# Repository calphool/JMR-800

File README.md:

# JMR-800

**JMR-800** is a modern, open-source clone of the Roland PG-800 hardware programmer, built around the Teensy 4.1 microcontroller. It provides real-time 
parameter control for vintage Roland synthesizers such as the JX-8P, MKS-70, and JX-10 using the original PG-800 communication protocol.

The JMR-800 replicates the original PG-800's functionality and physical interface, enabling direct, tactile editing of synthesizer parameters through a 
hands-on control surface.

## Features

- Compatible with Roland synths that support the PG-800 interface
- Built on Teensy 4.1 with fast, low-latency signal handling
- Accurate emulation of the PG-800 protocol (Clock, Ready, and Data lines)
- Designed for easy assembly and expansion
- Open hardware and firmware

## Status

This project is currently in active development. Basic communication and parameter changes are being validated. Contributions, forks, and collaboration are 
welcome.

April 10, 2025

- Redesigned PCB to get rid of the 74HC165 input bit shifter and replaced it with another analog mux/demux.  The total number of parameters that can be 
tweaked with the JX8P with the Vecoven PWM enhancement is 52.  So, I need to support at least 52 pots, and I can only support 48 with three muxes.  I mean
there are enough ADCs on the Teensy 4.1, that I probably could hack it and get those last 4 with separate ADC pins on the Teensy, but that's a pretty 
ineligant design, so I'll just add another mux/demux, get rid of the bit shifter, and limit my use of push buttons to just a few.  I technically only 
need one or two (the PG-800 only has 2), but I'll probably come up with a few odds and ends to implement (like maybe a way to load a whole sound from 
the JMR-800 by tweaking all of the parameters based on loading something from an SD card or something), so having a few more won't hurt.

- Decided to lay out the whole interface with my 3D printer as a template first.  This will allow me to cut cleaner holes into the aluminum case I think.
I'm using an aluminum case from Jameco that looks pretty retro / period correct.

April 14, 2025

Worked on the aluminum case a bit today.  Ran out of potentiometers, so ordered some more.

April 17, 2025

Worked on the case some more.  Completed the potentiometer installation, got some knobs and installed them, though I don't like the fact that I didn't get 
an even number of red and blue, so I need to get another kit of them.  I also don't like the white ones, I think I'll remove those and replace with black.  
Finally, I couldn't find black 3mm screws, so I had to use stainless steel.  I'm going to change that, it ruins the asthetic.

Once I get all that settled, it's back to the software and firmware.  I redesigned the PCB about a week ago, but I think I'm going to need to do a slight 
additional redesign.  The four push buttons have two LEDs on them, a red one and a green one.  I really don't know exactly what I'm going to use them 
for yet, but I'm going to need an output shift register to manage all 8 of them (as well as current limiting resistors for each one, which would probably 
be best on the board rather than dangling and inline with the wires.

The software already works in a prototype way (two potentiometers that I tested with), so hopefully there won't be any surprises when I get all of them 
running.  I also added an additional 3.3V regulator that's optional on the new design, since I'm not altogether sure that the tiny little regulator on the 
Teensy can handle all the load I'm throwing at it.

April 29, 2025

Got the new PCB and the rest of the hardware put together.  I wrote some temporary code that implements a "TEST MODE" that shows the condition of all 
the knobs.

May 3, 2025

I've updated the code quite a bit.  It now has 3 modes.  Run mode, Test mode, and Config mode.  I've been working on the Config mode.  You can change 
into these different modes by pressing Button 1 and Button 2 simultaneously.  When you configure a knob, you can change its name, its command byte, 
and select which type of knob it is.  I've got the command byte selection finished, and I'm working on the name update code now.  Once I get all the 
config stuff finished (perhaps this evening), I'll begin working on the Run mode.  This stuff was prototyped already with the earlier version of the 
board, so I'm pretty sure the code for interacting with the synth will work.

I may eventually implement some kind of "preset mode" that allows you to scroll through a given configuration of knobs, select it, and it would play 
all 56 knobs into the synthesizer.  This may be a submenu of the Run mode.  One step at a time of course...

May 5, 2025

***It's alive***!  I got the first fully functional code put together and just did about 15 minutes of testing.  It definitely works.  Though there's 
plenty to tweak.  Right now it's ignoring the parameter type and just sending values from 0 - 127, which does work, but it causes the screen to flicker 
on the synth for the parameters that only have a few set values.  I'm also wondering about how to manage noise from the potentiometers.  Although I 
used a smoothing algorithm, which does make them a lot less noisy, you still get odd little blips from time to time, and since they take whatever 
value the knob is at at the time, if you've just changed patches it can make a dramatic change to the sound.  I wonder if I should implement a 
kind of "lock / unlock" with one of the switches.  I could use green for "I'm unlocked and sending data to the synth" vs red for "I'm currently 
locked and not sending anything to the synth."

Lots and lots of small tweaks to work on now, but at least it's working.  The PWM mod that I installed from https://www.vecoven.com/superjx/styled/pwm.html
is pretty cool, especially with knobs that tweak its behavior in real time.

The other tweaks that the vecoven upgrade made to my firmware on my synth still takes some getting used to.  I'm going to have to read through the 
manuals for the vecoven upgrade really carefully, because it's pretty easy to get lost in the menus.  Maybe I could implement a "notepad" in the 
OLED screen of the JMR800 so it can remind me of stuff for the Vecoven upgrade.

One thing that I noticed that I'm going to have to deal with is the fact that not all the pots return the full range from 0 - 127 when sent through the 
ADC.  They came in a big bag from Aliexpress, so they're probably pretty low quality.  I'm going to need to implement some way to measure their min and 
max values, probably in the config mode, and then scale the pot value for each pot in software.

May 11, 2025

Finished all the screen stuff for Run mode, which is a pretty big milestone.  Also added an SVG file that represents the console layout. Working on an 
overlay using a Glowforge and acrylic.

May 14, 2025

May 22, 2025

I'm beginning to consider a major refactor of the software.  It all works pretty well, but there are some things I'd like to do that require a cleaner code 
base.  Basically I cobbled together the different system modes using a sloppy FSM rather than doing proper object oriented development whereby I set up 
modes as objects, and modes have screens, and screens have widgets, and widgets interact with controls, and so on.  By doing this, I'd have an infinitely 
more expandable user interface, and I really would like to implement a few interesting ideas.

First, I'd like to make it so that there are a collection of pre-sets that can be played into the JX8P on demand (like button 2 does right now with the 
default sound load, but with many many different presets).  The other thing I'd really like to do is implement something analogous to an arpeggiator, but 
rather than changing notes, it would change settings on a parameter.  For example, let's say you want to vary any arbitrary parameter (say something weird 
like chorus) with something like an LFO.  Let us further consider that you don't want to use one of the three or four LFO options available in the synth 
hardware itself, bur instead you want to be able to apply any arbitrary waveform to that chorus.  Although the "waveform" will be small (only 32 steps), it 
can take any form, and you simply draw the waveform in.  Then, when you go to a parameter for a given control, you depress the encoder button, and it pops 
up with a menu that lets you choose which stepper-LFO you want to use for this parameter.

All of this will require some significant refactoring.  I also want to introduce a microSD to the Teensy so that all this stuff can be stored and retrieved.  
Keep an eye out for a major update to the code base soon.

## License

This project is released under the MIT License.

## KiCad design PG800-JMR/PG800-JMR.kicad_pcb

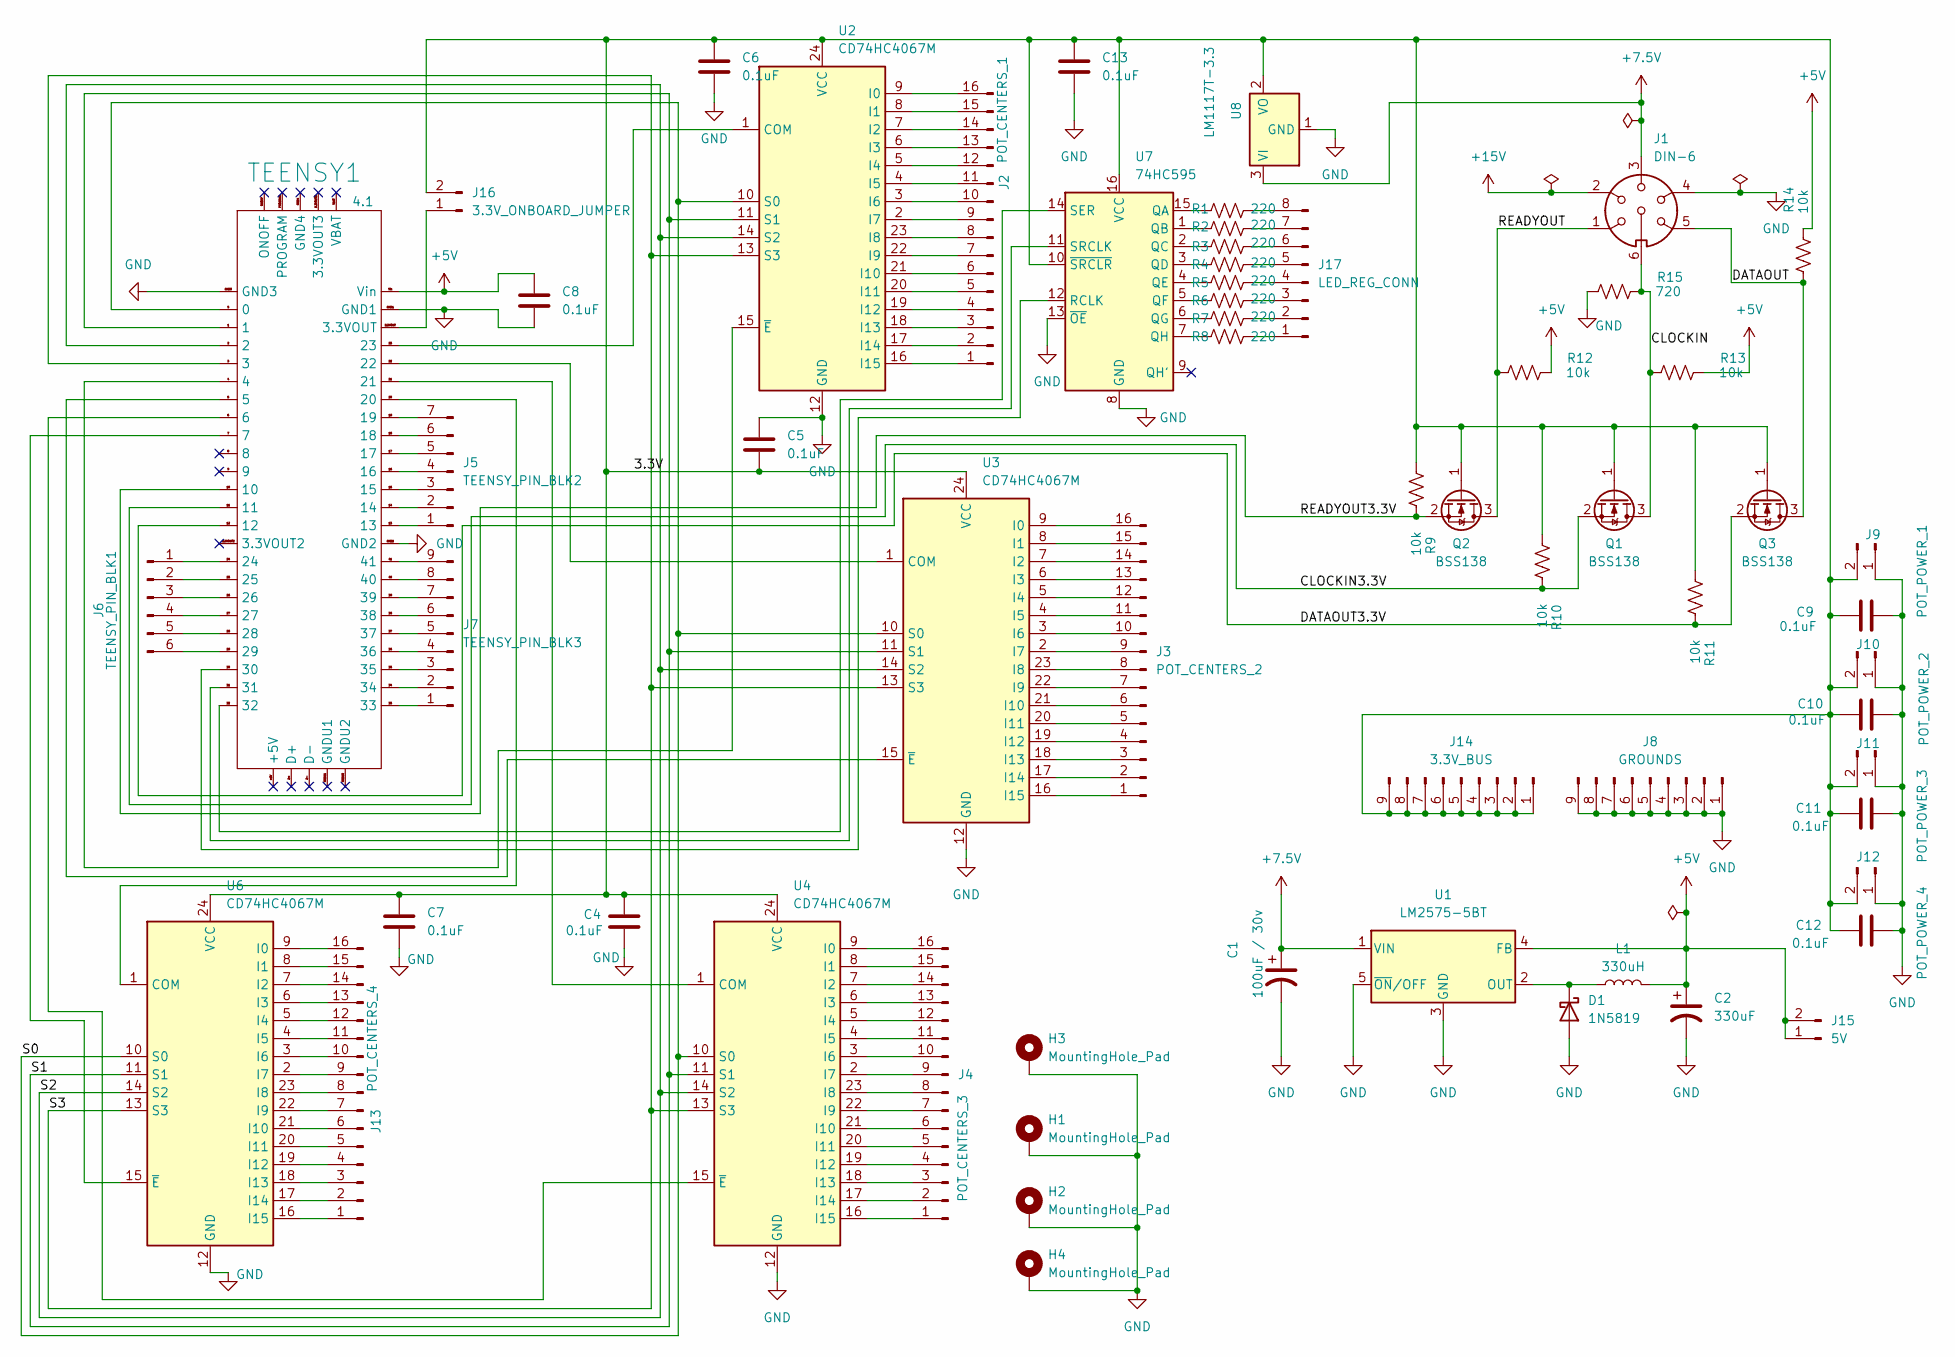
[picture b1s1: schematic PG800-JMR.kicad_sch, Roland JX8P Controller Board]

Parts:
C1: 100uF / 30v; CP_Radial_D10.0mm_P2.50mm
C2: 330uF; CP_Radial_D10.0mm_P5.00mm
C4, C5, C6, C7, C8, C9, C10, C11, C12, C13: 0.1uF; C_Disc_D5.0mm_W2.5mm_P2.50mm
D1: 1N5819; D_DO-15_P10.16mm_Horizontal
H1, H2, H3, H4: MountingHole_Pad; MountingHole_3.5mm_Pad
J1: DIN-6
J2: POT_CENTERS_1; PinHeader_1x16_P2.54mm_Vertical
J3: POT_CENTERS_2; PinHeader_1x16_P2.54mm_Vertical
J4: POT_CENTERS_3; PinHeader_1x16_P2.54mm_Vertical
J5: TEENSY_PIN_BLK2; PinHeader_1x07_P2.54mm_Vertical
J6: TEENSY_PIN_BLK1; PinHeader_1x06_P2.54mm_Vertical
J7: TEENSY_PIN_BLK3; PinHeader_1x09_P2.54mm_Vertical
J8: GROUNDS; PinHeader_1x09_P2.54mm_Vertical
J9: POT_POWER_1; PinHeader_1x02_P2.54mm_Vertical
J10: POT_POWER_2; PinHeader_1x02_P2.54mm_Vertical
J11: POT_POWER_3; PinHeader_1x02_P2.54mm_Vertical
J12: POT_POWER_4; PinHeader_1x02_P2.54mm_Vertical
J13: POT_CENTERS_4; PinHeader_1x16_P2.54mm_Vertical
J14: 3.3V_BUS; PinHeader_1x09_P2.54mm_Vertical
J15: 5V; PinHeader_1x02_P2.54mm_Vertical
J16: 3.3V_ONBOARD_JUMPER; PinHeader_1x02_P2.54mm_Vertical
J17: LED_REG_CONN; PinHeader_1x08_P2.54mm_Vertical
L1: 330uH; L_Radial_D12.0mm_P5.00mm_Fastron_11P
Q1, Q2, Q3: BSS138; SOT-23
R1, R2, R3, R4, R5, R6, R7, R8: 220; R_Axial_DIN0204_L3.6mm_D1.6mm_P2.54mm_Vertical
R9, R10, R11, R12, R13, R14: 10k; R_Axial_DIN0204_L3.6mm_D1.6mm_P7.62mm_Horizontal
R15: 720; R_Axial_DIN0204_L3.6mm_D1.6mm_P2.54mm_Vertical
TEENSY1: 4.1; Teensy4.1
U1: LM2575-5BT; TO-220-5_Vertical
U2, U3, U4, U6: CD74HC4067M; SOIC-24W_7.5x15.4mm_P1.27mm
U7: 74HC595; DIP-16_W7.62mm
U8: LM1117T-3.3; TO-220-3_Vertical

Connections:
+5V: C2.1, C8.1, J15.1, J15.2, L1.2, R12.1, R13.1, R14.1, TEENSY1.Vin, U1.4 (FB)
+7.5V: C1.1, J1.3, U1.1 (VIN), U8.3 (VI)
+15V: J1.2
/3.3V: C4.1, C5.2, C6.1, C7.1, C9.1, C10.1, C11.1, C12.1, C13.1, J9.2, J10.2, J11.2, J12.2, J14.1, J14.2, J14.3, J14.4, J14.5, J14.6, J14.7, J14.8, J14.9, J16.2, Q1.1 (G), Q2.1 (G), Q3.1 (G), R9.2, R10.2, R11.2, U2.24 (VCC), U3.24 (VCC), U4.24 (VCC), U6.24 (VCC), U7.10 (~SRCLR), U7.16 (VCC), U8.2 (VO)
/CLOCKIN: J1.6, Q1.3 (D), R13.2, R15.1
/CLOCKIN3.3V: Q1.2 (S), R10.1, TEENSY1.11
/DATAOUT: J1.5, Q3.3 (D), R14.2
/DATAOUT3.3V: Q3.2 (S), R11.1, TEENSY1.12
/READYOUT: J1.1, Q2.3 (D), R12.2
/READYOUT3.3V: Q2.2 (S), R9.1, TEENSY1.10
/S0: TEENSY1.0, U2.10 (S0), U3.10 (S0), U4.10 (S0), U6.10 (S0)
/S1: TEENSY1.1, U2.11 (S1), U3.11 (S1), U4.11 (S1), U6.11 (S1)
/S2: TEENSY1.2, U2.14 (S2), U3.14 (S2), U4.14 (S2), U6.14 (S2)
/S3: TEENSY1.3, U2.13 (S3), U3.13 (S3), U4.13 (S3), U6.13 (S3)
GND: C1.2, C2.2, C4.2, C5.1, C6.2, C7.2, C8.2, C9.2, C10.2, C11.2, C12.2, C13.2, D1.2 (A), H1.1, H2.1, H3.1, H4.1, J1.4, J8.1, J8.2, J8.3, J8.4, J8.5, J8.6, J8.7, J8.8, J8.9, J9.1, J10.1, J11.1, J12.1, R15.2, TEENSY1.GND1, TEENSY1.GND2, TEENSY1.GND3, U1.3 (GND), U1.5 (~ON/OFF), U2.12 (GND), U3.12 (GND), U4.12 (GND), U6.12 (GND), U7.8 (GND), U7.13 (~OE), U8.1 (GND)
unnamed: D1.1 (K), L1.1, U1.2 (OUT)
unnamed: J2.1, U2.16 (I15)
unnamed: J2.2, U2.17 (I14)
unnamed: J2.3, U2.18 (I13)
unnamed: J2.4, U2.19 (I12)
unnamed: J2.5, U2.20 (I11)
unnamed: J2.6, U2.21 (I10)
unnamed: J2.7, U2.22 (I9)
unnamed: J2.8, U2.23 (I8)
unnamed: J2.9, U2.2 (I7)
unnamed: J2.10, U2.3 (I6)
unnamed: J2.11, U2.4 (I5)
unnamed: J2.12, U2.5 (I4)
unnamed: J2.13, U2.6 (I3)
unnamed: J2.14, U2.7 (I2)
unnamed: J2.15, U2.8 (I1)
unnamed: J2.16, U2.9 (I0)
unnamed: J3.1, U3.16 (I15)
unnamed: J3.2, U3.17 (I14)
unnamed: J3.3, U3.18 (I13)
unnamed: J3.4, U3.19 (I12)
unnamed: J3.5, U3.20 (I11)
unnamed: J3.6, U3.21 (I10)
unnamed: J3.7, U3.22 (I9)
unnamed: J3.8, U3.23 (I8)
unnamed: J3.9, U3.2 (I7)
unnamed: J3.10, U3.3 (I6)
unnamed: J3.11, U3.4 (I5)
unnamed: J3.12, U3.5 (I4)
unnamed: J3.13, U3.6 (I3)
unnamed: J3.14, U3.7 (I2)
unnamed: J3.15, U3.8 (I1)
unnamed: J3.16, U3.9 (I0)
unnamed: J4.1, U4.16 (I15)
unnamed: J4.2, U4.17 (I14)
unnamed: J4.3, U4.18 (I13)
unnamed: J4.4, U4.19 (I12)
unnamed: J4.5, U4.20 (I11)
unnamed: J4.6, U4.21 (I10)
unnamed: J4.7, U4.22 (I9)
unnamed: J4.8, U4.23 (I8)
unnamed: J4.9, U4.2 (I7)
unnamed: J4.10, U4.3 (I6)
unnamed: J4.11, U4.4 (I5)
unnamed: J4.12, U4.5 (I4)
unnamed: J4.13, U4.6 (I3)
unnamed: J4.14, U4.7 (I2)
unnamed: J4.15, U4.8 (I1)
unnamed: J4.16, U4.9 (I0)
unnamed: J5.1, TEENSY1.13
unnamed: J5.2, TEENSY1.14
unnamed: J5.3, TEENSY1.15
unnamed: J5.4, TEENSY1.16
unnamed: J5.5, TEENSY1.17
unnamed: J5.6, TEENSY1.18
unnamed: J5.7, TEENSY1.19
unnamed: J6.1, TEENSY1.24
unnamed: J6.2, TEENSY1.25
unnamed: J6.3, TEENSY1.26
unnamed: J6.4, TEENSY1.27
unnamed: J6.5, TEENSY1.28
unnamed: J6.6, TEENSY1.29
unnamed: J7.1, TEENSY1.33
unnamed: J7.2, TEENSY1.34
unnamed: J7.3, TEENSY1.35
unnamed: J7.4, TEENSY1.36
unnamed: J7.5, TEENSY1.37
unnamed: J7.6, TEENSY1.38
unnamed: J7.7, TEENSY1.39
unnamed: J7.8, TEENSY1.40
unnamed: J7.9, TEENSY1.41
unnamed: J13.1, U6.16 (I15)
unnamed: J13.2, U6.17 (I14)
unnamed: J13.3, U6.18 (I13)
unnamed: J13.4, U6.19 (I12)
unnamed: J13.5, U6.20 (I11)
unnamed: J13.6, U6.21 (I10)
unnamed: J13.7, U6.22 (I9)
unnamed: J13.8, U6.23 (I8)
unnamed: J13.9, U6.2 (I7)
unnamed: J13.10, U6.3 (I6)
unnamed: J13.11, U6.4 (I5)
unnamed: J13.12, U6.5 (I4)
unnamed: J13.13, U6.6 (I3)
unnamed: J13.14, U6.7 (I2)
unnamed: J13.15, U6.8 (I1)
unnamed: J13.16, U6.9 (I0)
unnamed: J16.1, TEENSY1.3.3VOUT
unnamed: J17.1, R8.2
unnamed: J17.2, R7.2
unnamed: J17.3, R6.2
unnamed: J17.4, R5.2
unnamed: J17.5, R4.2
unnamed: J17.6, R3.2
unnamed: J17.7, R2.2
unnamed: J17.8, R1.2
unnamed: TEENSY1.23, U2.1 (COM)
unnamed: TEENSY1.4, U2.15 (~E)
unnamed: TEENSY1.22, U3.1 (COM)
unnamed: TEENSY1.5, U3.15 (~E)
unnamed: TEENSY1.21, U4.1 (COM)
unnamed: TEENSY1.6, U4.15 (~E)
unnamed: TEENSY1.20, U6.1 (COM)
unnamed: TEENSY1.7, U6.15 (~E)
unnamed: R1.1, U7.15 (QA)
unnamed: R2.1, U7.1 (QB)
unnamed: R3.1, U7.2 (QC)
unnamed: R4.1, U7.3 (QD)
unnamed: R5.1, U7.4 (QE)
unnamed: R6.1, U7.5 (QF)
unnamed: R7.1, U7.6 (QG)
unnamed: R8.1, U7.7 (QH)
unnamed: TEENSY1.30, U7.12 (RCLK)
unnamed: TEENSY1.32, U7.14 (SER)
unnamed: TEENSY1.31, U7.11 (SRCLK)

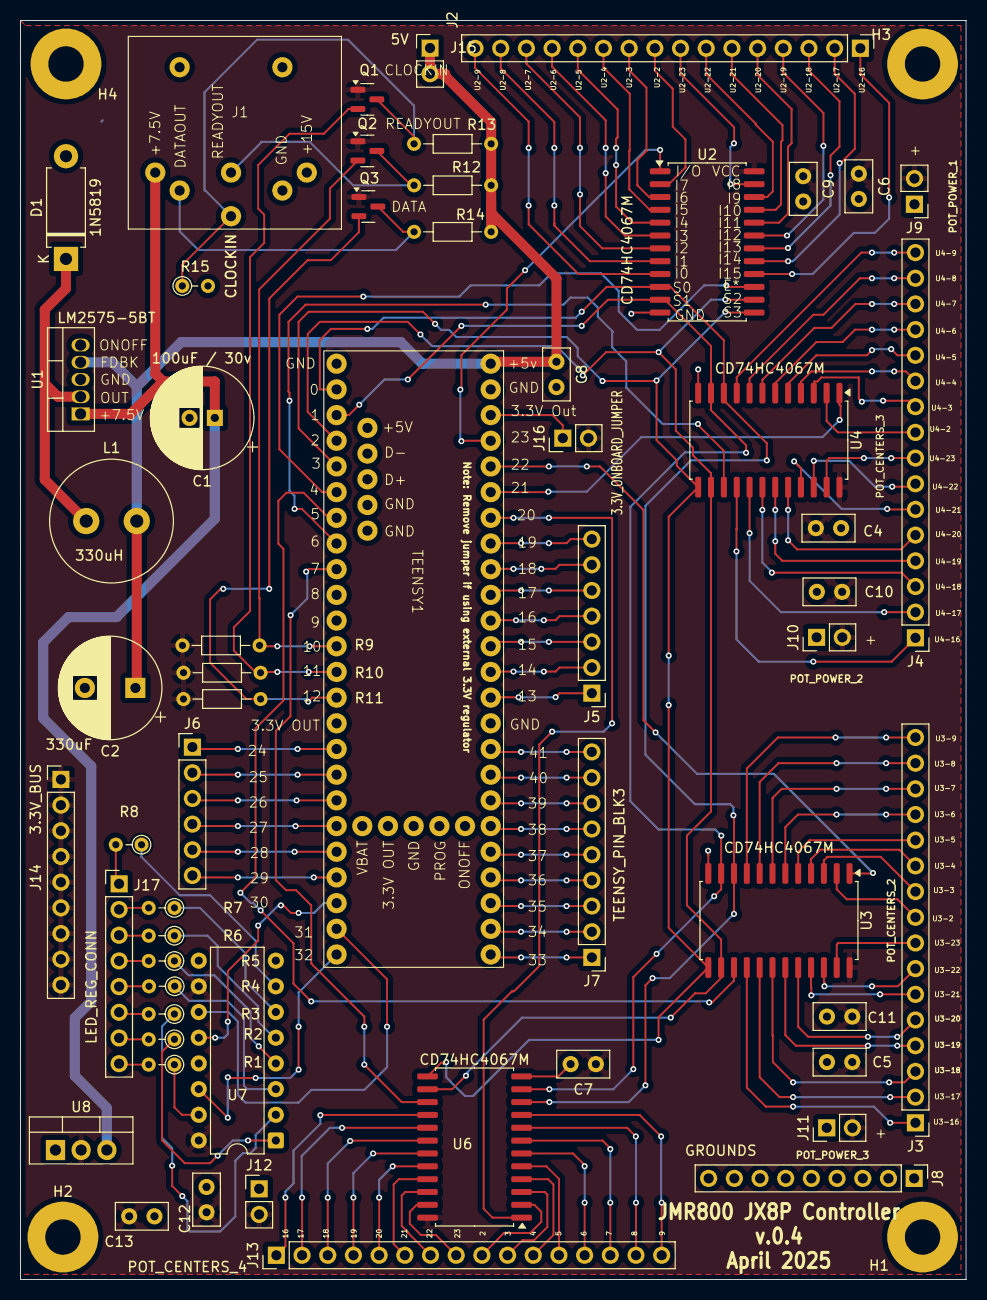
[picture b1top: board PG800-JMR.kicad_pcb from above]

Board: 2 copper layers, 93.5 x 124.5 mm, 61 parts (0 on the bottom side), 129 nets.

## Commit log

2025-04-03 added schematics and PCBs in KiCad format
2025-04-04 working code
2025-04-04 updated kicad drawings, tweaked code slightly
2025-04-04 updated picture
2025-04-04 updated pictures
2025-04-05 update for PWM upgrade
2025-04-07 got code working for 2 pots, ready for larger number
2025-04-08 updated PCB design, added optional 3.3V regulator, added another mux
2025-04-17 readme update
2025-04-18 updated 3d image
2025-04-26 Fixed LM1117-3.3, pins in wrong order
2025-04-26 updated code to support 4 muxes / 64 knobs
2025-04-26 changed picture
2025-04-30 updated code for new hardware
2025-05-01 completed test mode functionality
2025-05-01 added SH1106 editor
2025-05-01 updated JMR800.ino
2025-05-02 added skeleton code for different modes (test, config, run)
2025-05-02 added shell of mode handling
2025-05-02 added code to handle active knob in config screen
2025-05-02 added knob configuration structures
2025-05-02 changes for knob config screen
2025-05-03 Updated config handler. Cmd Byte working now
2025-05-03 added EEProm code to store and restore settings
2025-05-03 added beginning functionality for config name
2025-05-04 finished name change code
2025-05-04 added type code
2025-05-05 finished type handling
2025-05-05 first fully working version
2025-05-05 first working version - updated readme
2025-05-05 tweaked readme
2025-05-06 updated code, including 'send all values' in Run Mode
2025-05-07 updated code to enable Button 2 to send a basic sound to work from
2025-05-07 added hysteresis code to get rid of noisy knob turns
2025-05-07 fixed commented out cmds in case we need to reload eeprom
2025-05-07 broke up files into main, display, global, and hardware
2025-05-10 minor changes
2025-05-10 updated running mode display for 0-to-10 type codes
2025-05-12 completed Run mode, pretty big milestone
2025-05-12 updated readme and added ControlPanel.svg
2025-05-12 made small tweak to button placement
2025-05-13 created a slightly customized control panel SVG for GlowForge to deal with the fact that knobs aren't perfectly aligned
2025-05-13 small update
2025-05-15 updated photo
2025-05-22 updated .gitignore
2025-05-22 small change
